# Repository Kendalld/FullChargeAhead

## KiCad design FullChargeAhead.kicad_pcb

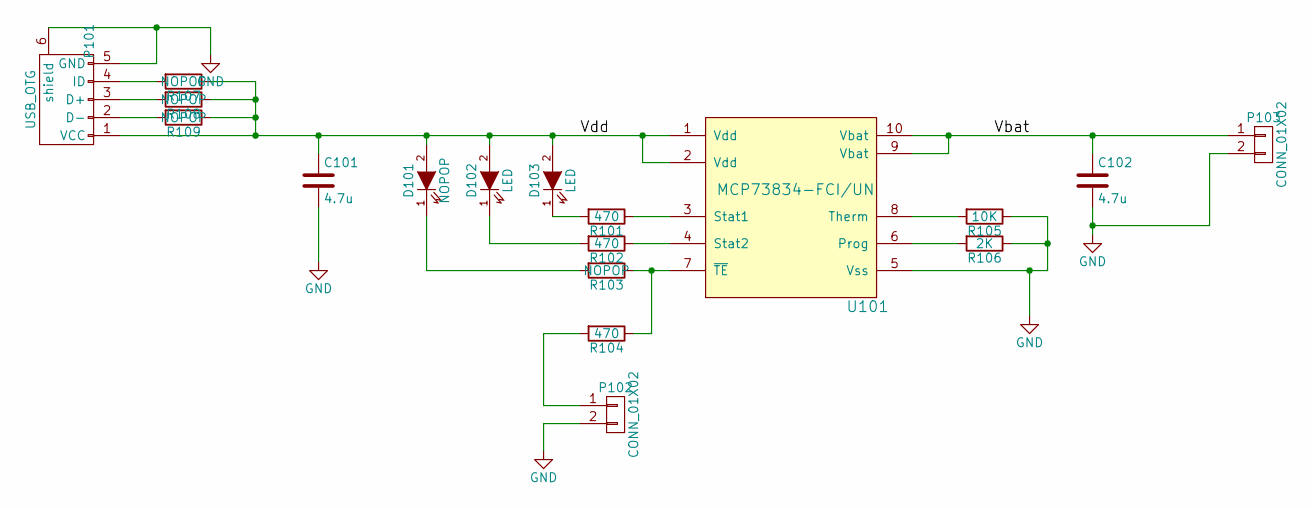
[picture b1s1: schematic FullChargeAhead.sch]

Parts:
C101, C102: 4.7u; C_1206_HandSoldering
D101: NOPOP; LED_0805
D102, D103: LED; LED_0805
P101: USB_OTG; USB_Micro-B; MPN Value
P102, P103: CONN_01X02; Pin_Header_Straight_1x02
R101, R102, R104: 470; R_0805_HandSoldering
R103, R107, R108, R109: NOPOP; R_0805_HandSoldering
R105: 10K; R_0805_HandSoldering
R106: 2K; R_0805_HandSoldering
U101: MCP73834-FCI/UN; MSOP-10_3x3mm_Pitch0.5mm

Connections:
/Vbat: C102.1, P103.1, U101.9 (Vbat), U101.10 (Vbat)
/Vdd: C101.1, D101.2 (A), D102.2 (A), D103.2 (A), P101.1 (VCC), R107.1, R108.1, R109.1, U101.1 (Vdd), U101.2 (Vdd)
GND: C101.2, C102.2, P101.5 (GND), P101.6 (shield), P102.2, P103.2, R105.1, R106.1, U101.5 (Vss)
unnamed: D101.1 (K), R103.2
unnamed: D102.1 (K), R102.2
unnamed: D103.1 (K), R101.2
unnamed: P101.2 (D-), R109.2
unnamed: P101.3 (D+), R108.2
unnamed: P101.4 (ID), R107.2
unnamed: P102.1, R104.2
unnamed: R101.1, U101.3 (Stat1)
unnamed: R102.1, U101.4 (Stat2)
unnamed: R103.1, R104.1, U101.7 (~TE)
unnamed: R105.2, U101.8 (Therm)
unnamed: R106.2, U101.6 (Prog)

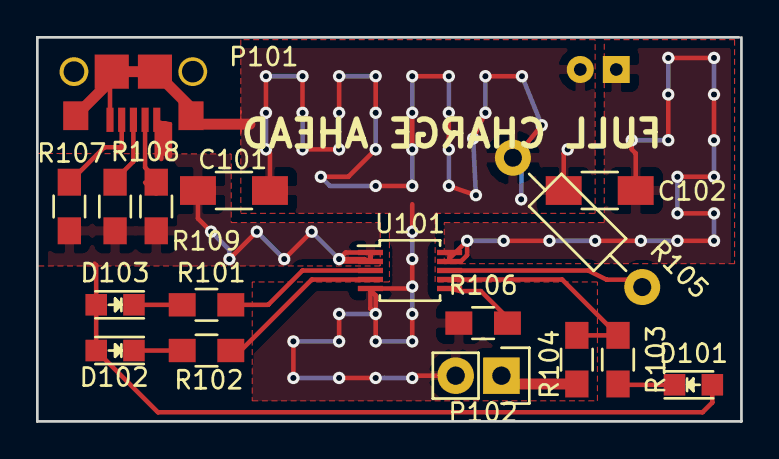
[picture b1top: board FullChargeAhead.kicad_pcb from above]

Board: 2 copper layers, 39.1 x 21.3 mm, 18 parts (1 on the bottom side), 15 nets.

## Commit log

2016-03-03 FCA up to placing footprints on PCB new
2016-03-03 Corrected the spelling of .gitinore file
2016-03-06 PBC finished and submitted to OSH park. Note the board is smaller than CE example and may not work as well as a result.
